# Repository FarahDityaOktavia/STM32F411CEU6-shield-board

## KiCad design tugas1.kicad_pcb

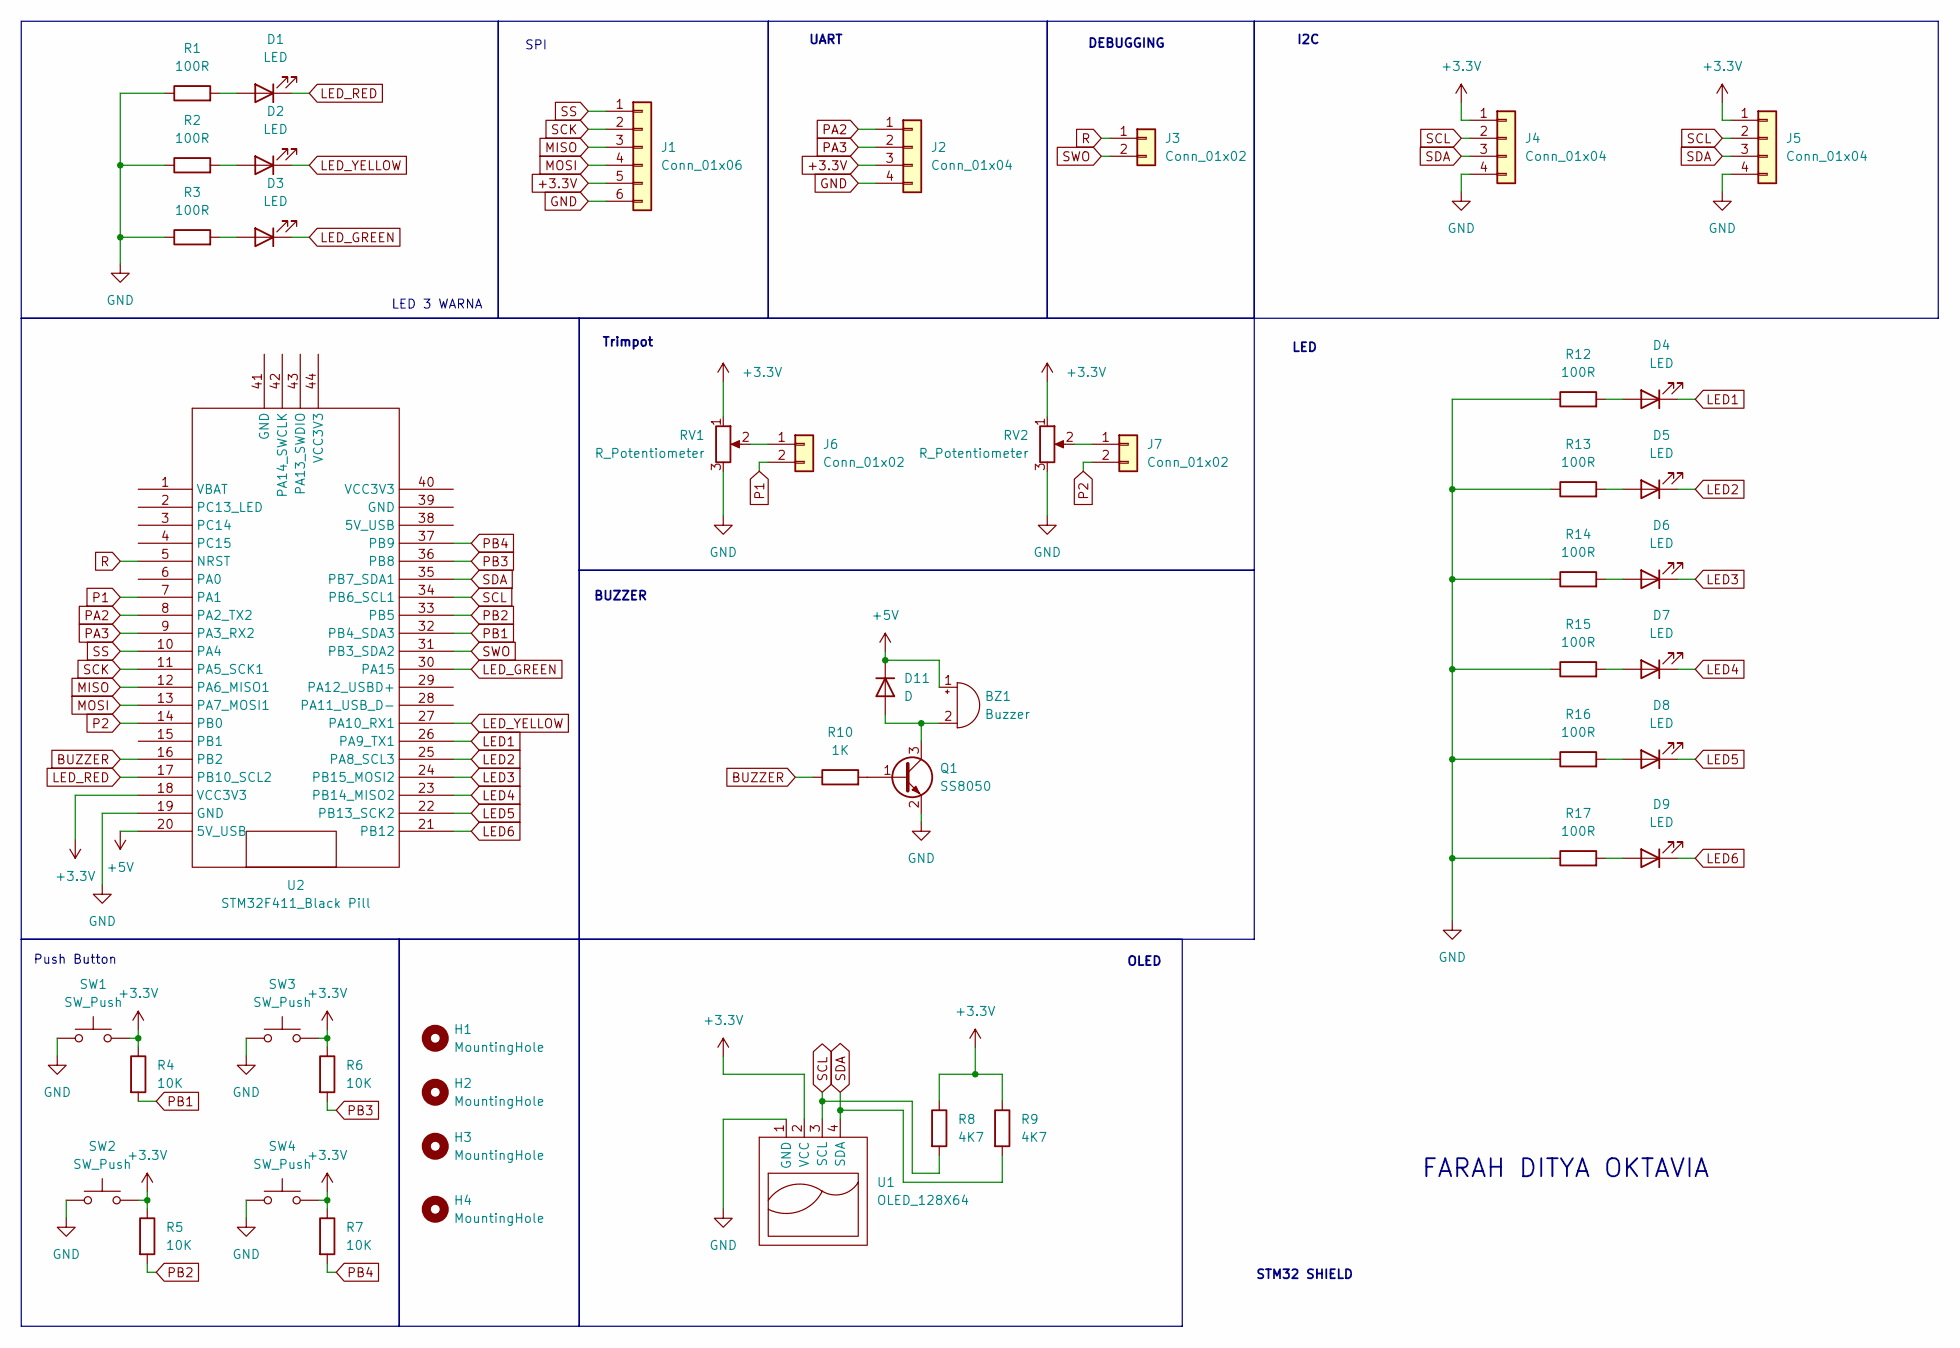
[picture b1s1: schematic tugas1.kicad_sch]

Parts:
BZ1: Buzzer; Buzzer_12x9.5RM7.6
D1, D2, D3, D4, D5, D6, D7, D8, D9: LED; LED_D3.0mm
D11: D; D_5W_P12.70mm_Horizontal
H1, H2, H3, H4: MountingHole; MountingHole_2.2mm_M2_DIN965_Pad
J1: Conn_01x06; JST_XH_B6B-XH-A_1x06_P2.50mm_Vertical
J2, J4, J5: Conn_01x04; JST_XH_B4B-XH-A_1x04_P2.50mm_Vertical
J3, J6, J7: Conn_01x02; JST_XH_B2B-XH-A_1x02_P2.50mm_Vertical
Q1: SS8050; TO-92L_Inline_Wide
R1, R2, R3, R12, R13, R14, R15, R16, R17: 100R; R_1206_3216Metric
R4, R5, R6, R7: 10K; R_1206_3216Metric
R8, R9: 4K7; R_Axial_DIN0204_L3.6mm_D1.6mm_P5.08mm_Horizontal
R10: 1K; R_Axial_DIN0204_L3.6mm_D1.6mm_P5.08mm_Horizontal
RV1, RV2: R_Potentiometer; Potentiometer_Bourns_3386P_V
SW1, SW2, SW3, SW4: SW_Push; SW_PUSH_6mm_H4.3mm
U1: OLED_128X64; 128x64OLED
U2: STM32F411_Black Pill

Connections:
+3.3V: J1.5, J2.3, J4.1, J5.1, R4.1, R5.1, R6.1, R7.1, R8.1, R9.1, RV1.1, RV2.1, SW1.2, SW2.2, SW3.2, SW4.2, U1.2 (VCC), U2.18 (VCC3V3)
+5V: BZ1.1 (+), D11.1 (K), U2.20 (5V_USB)
BUZZER: R10.1, U2.16 (PB2)
GND: J1.6, J2.4, J4.4, J5.4, Q1.2 (E), R1.1, R2.1, R3.1, R12.1, R13.1, R14.1, R15.1, R16.1, R17.1, RV1.3, RV2.3, SW1.1, SW2.1, SW3.1, SW4.1, U1.1 (GND), U2.19 (GND)
LED1: D4.1 (K), U2.26 (PA9_TX1)
LED2: D5.1 (K), U2.25 (PA8_SCL3)
LED3: D6.1 (K), U2.24 (PB15_MOSI2)
LED4: D7.1 (K), U2.23 (PB14_MISO2)
LED5: D8.1 (K), U2.22 (PB13_SCK2)
LED6: D9.1 (K), U2.21 (PB12)
LED_GREEN: D3.1 (K), U2.30 (PA15)
LED_RED: D1.1 (K), U2.17 (PB10_SCL2)
LED_YELLOW: D2.1 (K), U2.27 (PA10_RX1)
MISO: J1.3, U2.12 (PA6_MISO1)
MOSI: J1.4, U2.13 (PA7_MOSI1)
unnamed: BZ1.2 (-), D11.2 (A), Q1.3 (C)
unnamed: D1.2 (A), R1.2
unnamed: D2.2 (A), R2.2
unnamed: D3.2 (A), R3.2
unnamed: D4.2 (A), R12.2
unnamed: D5.2 (A), R13.2
unnamed: D6.2 (A), R14.2
unnamed: D7.2 (A), R15.2
unnamed: D8.2 (A), R16.2
unnamed: D9.2 (A), R17.2
unnamed: J6.1, RV1.2
unnamed: J7.1, RV2.2
unnamed: Q1.1 (B), R10.2
P1: J6.2, U2.7 (PA1)
P2: J7.2, U2.14 (PB0)
PA2: J2.1, U2.8 (PA2_TX2)
PA3: J2.2, U2.9 (PA3_RX2)
PB1: R4.2, U2.32 (PB4_SDA3)
PB2: R5.2, U2.33 (PB5)
PB3: R6.2, U2.36 (PB8)
PB4: R7.2, U2.37 (PB9)
R: J3.1, U2.5 (NRST)
SCK: J1.2, U2.11 (PA5_SCK1)
SCL: J4.2, J5.2, R8.2, U1.3 (SCL), U2.34 (PB6_SCL1)
SDA: J4.3, J5.3, R9.2, U1.4 (SDA), U2.35 (PB7_SDA1)
SS: J1.1, U2.10 (PA4)
SWO: J3.2, U2.31 (PB3_SDA2)

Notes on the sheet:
BUZZER
Trimpot
UART
Push Button
DEBUGGING
LED
I2C
FARAH DITYA OKTAVIA
LED 3 WARNA
OLED
SPI
STM32 SHIELD

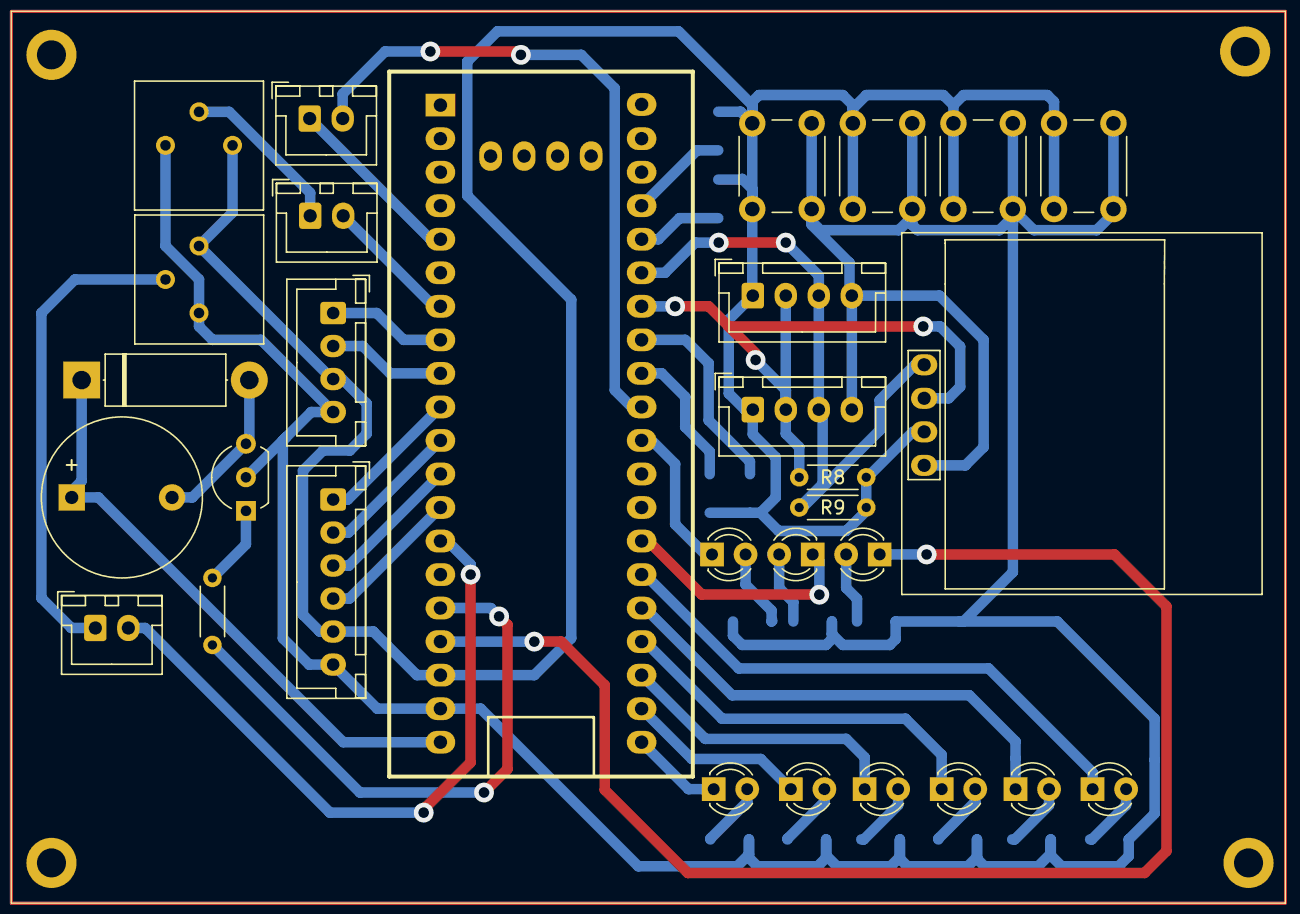
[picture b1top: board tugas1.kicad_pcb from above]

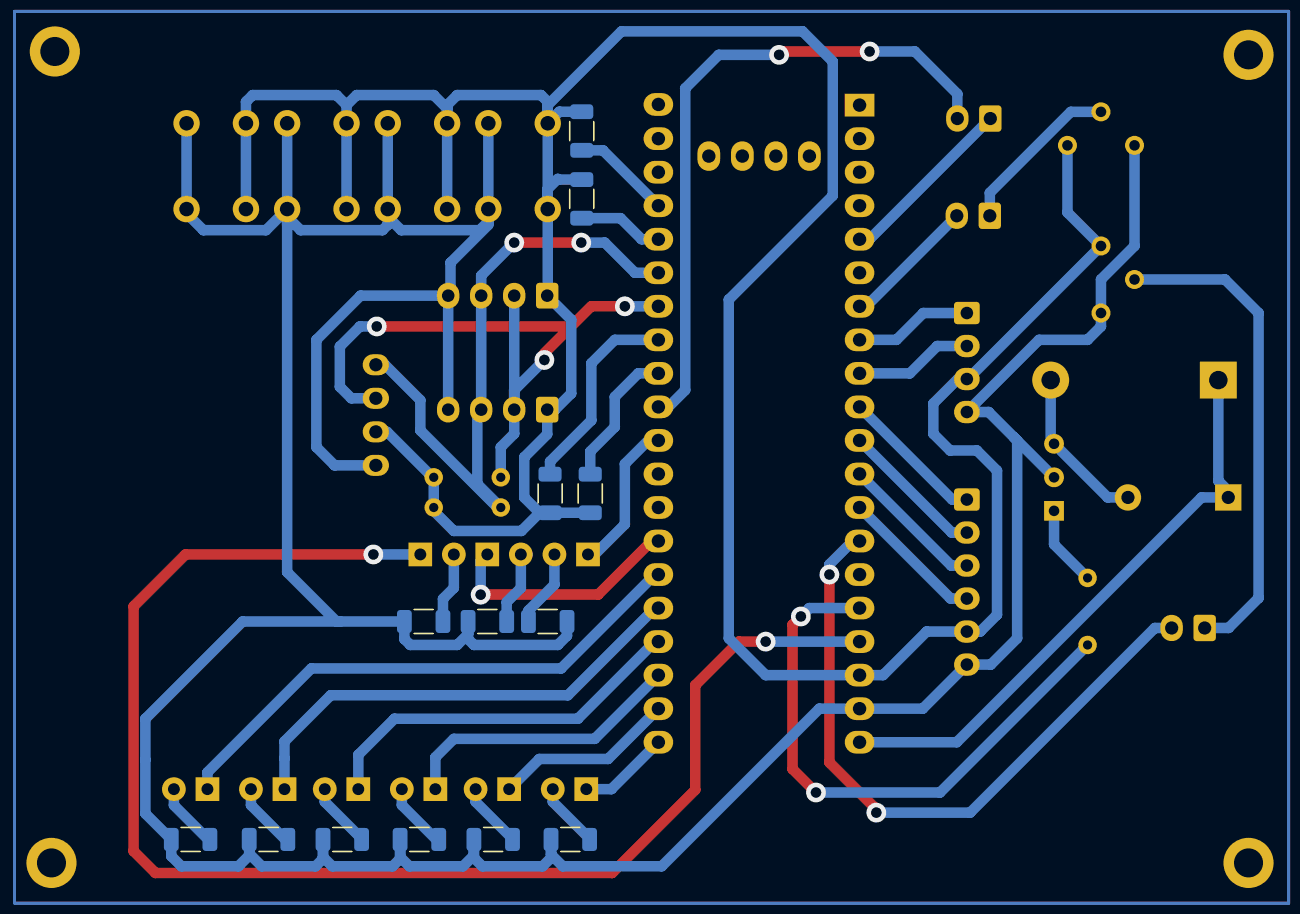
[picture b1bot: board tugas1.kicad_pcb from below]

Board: 2 copper layers, 47 parts (13 on the bottom side), 42 nets.

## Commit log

2024-11-26 Add files via upload
    upload file PCB
